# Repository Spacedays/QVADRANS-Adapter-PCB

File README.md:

This is an adapter board for the [QVADRANS 1.0/Lepton 3.0 board](https://community.simplefoc.com/t/qvadrans-v1-0-fka-lepton-3-0/3376) to break out connectors and pins to a usable/easily testable form factor. 

I've made a few of these successfully so far, but YMMV so make sure the board's what you want before having them made.

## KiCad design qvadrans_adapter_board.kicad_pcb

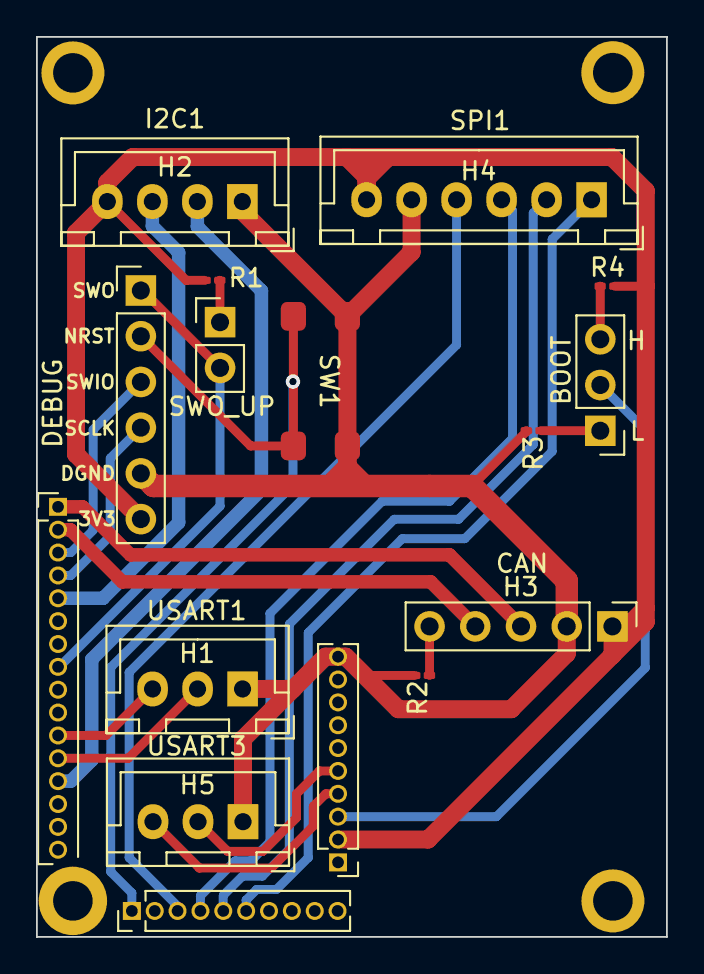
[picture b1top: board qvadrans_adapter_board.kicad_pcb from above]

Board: 2 copper layers, 35.0 x 50.0 mm, 18 parts (0 on the bottom side), 23 nets.

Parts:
H1: USART1; JST_XH_B3B-XH-A_1x03_P2.50mm_Vertical
H2: I2C1; JST_XH_B4B-XH-A_1x04_P2.50mm_Vertical
H3: CAN; PinHeader_1x05_P2.54mm_Vertical
H4: SPI1; JST_XH_B6B-XH-A_1x06_P2.50mm_Vertical
H5: USART3; JST_XH_B3B-XH-A_1x03_P2.50mm_Vertical
H6: DEBUG; PinHeader_1x06_P2.54mm_Vertical
JP0: BOOT; PinHeader_1x03_P2.54mm_Vertical
JP1: SWO_UP; PinHeader_1x02_P2.54mm_Vertical
M1: MountingHole_2.2mm_M2_DIN965_Pad
M2, M3, M4: MountingHole_2.2mm_M2_ISO7380_Pad
R1, R2, R3, R4: 10k; R_0201_0603Metric_Pad0.64x0.40mm_HandSolder
SW1: SW_SPST; Button_TTL3305_Tact_Switch
U1: QVADRANS_V1_headers

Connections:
3V3: H2.4, H3.1, H4.6, H6.6, R1.2, R4.2, U1.3V3
BOOT: JP0.2, U1.BOOT
CAN_RX: H3.3, U1.PA11
CAN_TX: H3.4, U1.PA12
DGND: H1.1, H2.1, H3.2, H4.5, H5.1, H6.5, R2.2, R3.2, SW1.2 (B), U1.DGND (DGND_ALT)
I2C1_SCL: H2.3, U1.PA15
I2C1_SDA: H2.2, U1.PB9
NRST: H6.2, SW1.1 (A), U1.NRST
unnamed: H3.5, R2.1
unnamed: JP0.1, R3.1
unnamed: JP0.3, R4.1
unnamed: JP1.1 (A), R1.1
PA4_SPI1_SS: H4.4, U1.PA4
PA5_SPI1_SCK: H4.3, U1.PA5
PA6_SPI1_MISO: H4.2, U1.PA6
PA7_SPI1_MOSI: H4.1, U1.PA7
SWCLK: H6.4, U1.PA14
SWDIO: H6.3, U1.PA13
SWO: H6.1, JP1.2 (B), U1.PB3
UART1RX: H1.2, U1.PB7
UART1TX: H1.3, U1.PB6
UART3RX: H5.2, U1.PB11
UART3TX: H5.3, U1.PB10
